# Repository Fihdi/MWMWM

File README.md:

# 6hp Wavefolder

MWMWM is a 7 to 1 Wavefolder based on [Daveys Deadband](https://github.com/DaveyGraham/Daveys_Deadband) and Buchlas wavefolding method. At the maximum amount of wavefolding, a single wave cycle gets converted into seven cycles on the output.

The **FOLD** and the **CV** knob settings control the amount of wavefolding. 

**OFFSET** is the second input and is summed to the **IN** signal. Like the **OFFSET** knob, it can be used to offset the **IN** signal.

Fully analog design allows for audio rate modulation. Every input and output jack is DC biased and thus the module can be used to modulate CV signals as well.

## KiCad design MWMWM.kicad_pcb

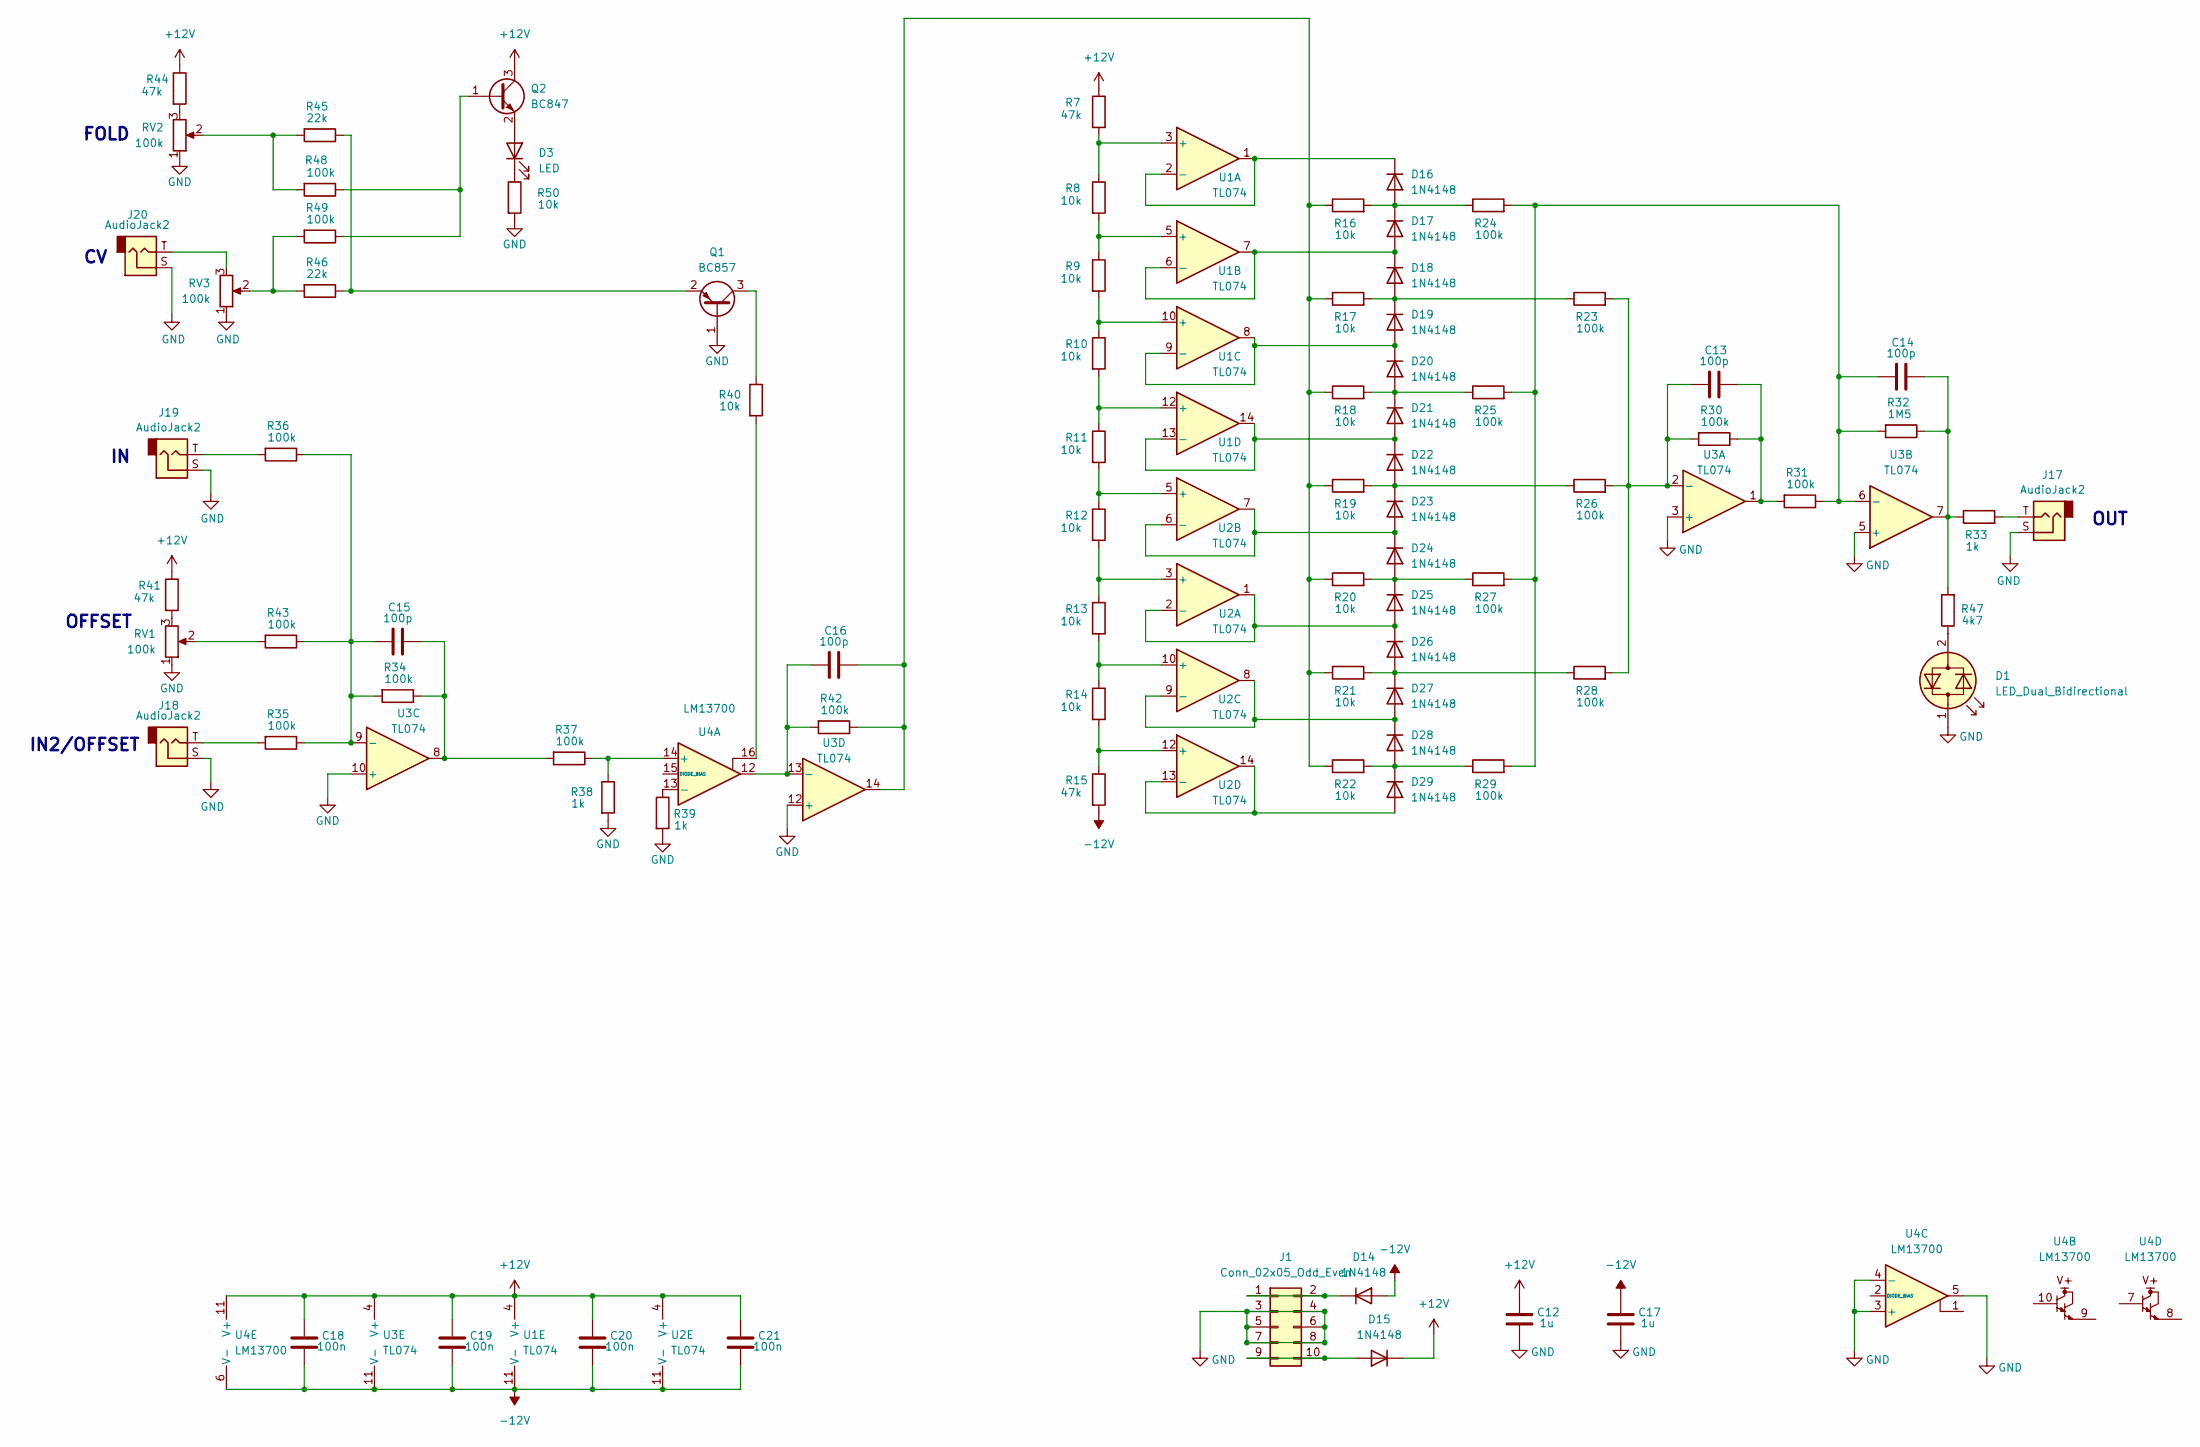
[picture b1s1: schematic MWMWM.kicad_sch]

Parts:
C12, C17: 1u; C_0805_2012Metric
C13, C14, C15, C16: 100p; C_0805_2012Metric
C18, C19, C20, C21: 100n; C_0805_2012Metric
D1: LED_Dual_Bidirectional; LED_D5.0mm
D3: LED; LED_D3.0mm
D14, D15, D16, D17, D18, D19, D20, D21, D22, D23, D24, D25, D26, D27, D28, D29: 1N4148; D_SOD-323_HandSoldering
J1: Conn_02x05_Odd_Even; IDC-Header_2x05_P2.54mm_Vertical
J17, J18, J19, J20: AudioJack2; MonoTRS
Q1: BC857; SOT-23
Q2: BC847; SOT-23
R7, R15, R41, R44: 47k; R_0805_2012Metric
R8, R9, R10, R11, R12, R13, R14, R16, R17, R18, R19, R20, R21, R22, R40, R50: 10k; R_0805_2012Metric
R23, R24, R25, R26, R27, R28, R29, R30, R31, R34, R35, R36, R37, R42, R43, R48, R49: 100k; R_0805_2012Metric
R32: 1M5; R_0805_2012Metric
R33, R38, R39: 1k; R_0805_2012Metric
R45, R46: 22k; R_0805_2012Metric
R47: 4k7; R_0805_2012Metric
RV1, RV2, RV3: 100k; Potentiometer_Alpha_RD901F-40-00D_Single_Vertical
U1, U2, U3: TL074; TSSOP-14_4.4x5mm_P0.65mm
U4: LM13700; SOIC-16_3.9x9.9mm_P1.27mm

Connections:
+12V: C12.1, C18.1, C19.1, C20.1, C21.1, D15.1 (K), Q2.3 (C), R7.1, R41.1, R44.1, U1.4 (V+), U2.4 (V+), U3.4 (V+), U4.11 (V+)
-12V: C17.1, C18.2, C19.2, C20.2, C21.2, D14.2 (A), R15.2, U1.11 (V-), U2.11 (V-), U3.11 (V-), U4.6 (V-)
GND: C12.2, C17.2, D1.1 (KA), J1.3, J1.4, J1.5, J1.6, J1.7, J1.8, J17.S, J18.S, J19.S, J20.S, Q1.1 (B), R38.2, R39.2, R50.2, RV1.1, RV2.1, RV3.1, U3.3 (+), U3.5 (+), U3.10 (+), U3.12 (+), U4.3 (+), U4.4 (-), U4.5
unnamed: C13.2, R30.1, R31.2, U3.1
unnamed: C14.2, R32.1, R33.1, R47.2, U3.7
unnamed: C15.2, R34.1, R37.2, U3.8
unnamed: C16.2, R16.1, R17.1, R18.1, R19.1, R20.1, R21.1, R22.1, R42.1, U3.14
unnamed: D1.2 (AK), R47.1
unnamed: D3.2 (A), Q2.2 (E)
unnamed: D3.1 (K), R50.1
unnamed: D14.1 (K), J1.1, J1.2
unnamed: D15.2 (A), J1.9, J1.10
unnamed: D16.2 (A), D17.1 (K), R16.2, R24.1
unnamed: D16.1 (K), U1.1, U1.2 (-)
unnamed: D17.2 (A), D18.1 (K), U1.6 (-), U1.7
unnamed: D18.2 (A), D19.1 (K), R17.2, R23.1
unnamed: D19.2 (A), D20.1 (K), U1.8, U1.9 (-)
unnamed: D20.2 (A), D21.1 (K), R18.2, R25.1
unnamed: D21.2 (A), D22.1 (K), U1.13 (-), U1.14
unnamed: D22.2 (A), D23.1 (K), R19.2, R26.1
unnamed: D23.2 (A), D24.1 (K), U2.6 (-), U2.7
unnamed: D24.2 (A), D25.1 (K), R20.2, R27.1
unnamed: D25.2 (A), D26.1 (K), U2.1, U2.2 (-)
unnamed: D26.2 (A), D27.1 (K), R21.2, R28.1
unnamed: D27.2 (A), D28.1 (K), U2.8, U2.9 (-)
unnamed: D28.2 (A), D29.1 (K), R22.2, R29.1
unnamed: D29.2 (A), U2.13 (-), U2.14
unnamed: J17.T, R33.2
unnamed: J18.T, R35.2
unnamed: J19.T, R36.2
unnamed: J20.T, RV3.3
unnamed: Q1.3 (C), R40.1
unnamed: Q1.2 (E), R45.1, R46.1
unnamed: Q2.1 (B), R48.1, R49.1
unnamed: R40.2, U4.16
unnamed: R41.2, RV1.3
unnamed: R43.2, RV1.2
unnamed: R44.2, RV2.3
unnamed: R45.2, R48.2, RV2.2
unnamed: R46.2, R49.2, RV3.2
unnamed: R7.2, R8.1, U1.3 (+)
unnamed: R8.2, R9.1, U1.5 (+)
unnamed: R9.2, R10.1, U1.10 (+)
unnamed: R10.2, R11.1, U1.12 (+)
unnamed: R12.2, R13.1, U2.3 (+)
unnamed: R11.2, R12.1, U2.5 (+)
unnamed: R13.2, R14.1, U2.10 (+)
unnamed: R14.2, R15.1, U2.12 (+)
unnamed: C13.1, R23.2, R26.2, R28.2, R30.2, U3.2 (-)
unnamed: C14.1, R24.2, R25.2, R27.2, R29.2, R31.1, R32.2, U3.6 (-)
unnamed: C15.1, R34.2, R35.1, R36.1, R43.1, U3.9 (-)
unnamed: C16.1, R42.2, U3.13 (-), U4.12
unnamed: R37.1, R38.1, U4.14 (+)
unnamed: R39.1, U4.13 (-)

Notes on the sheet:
OUT
IN2/OFFSET
OFFSET
FOLD

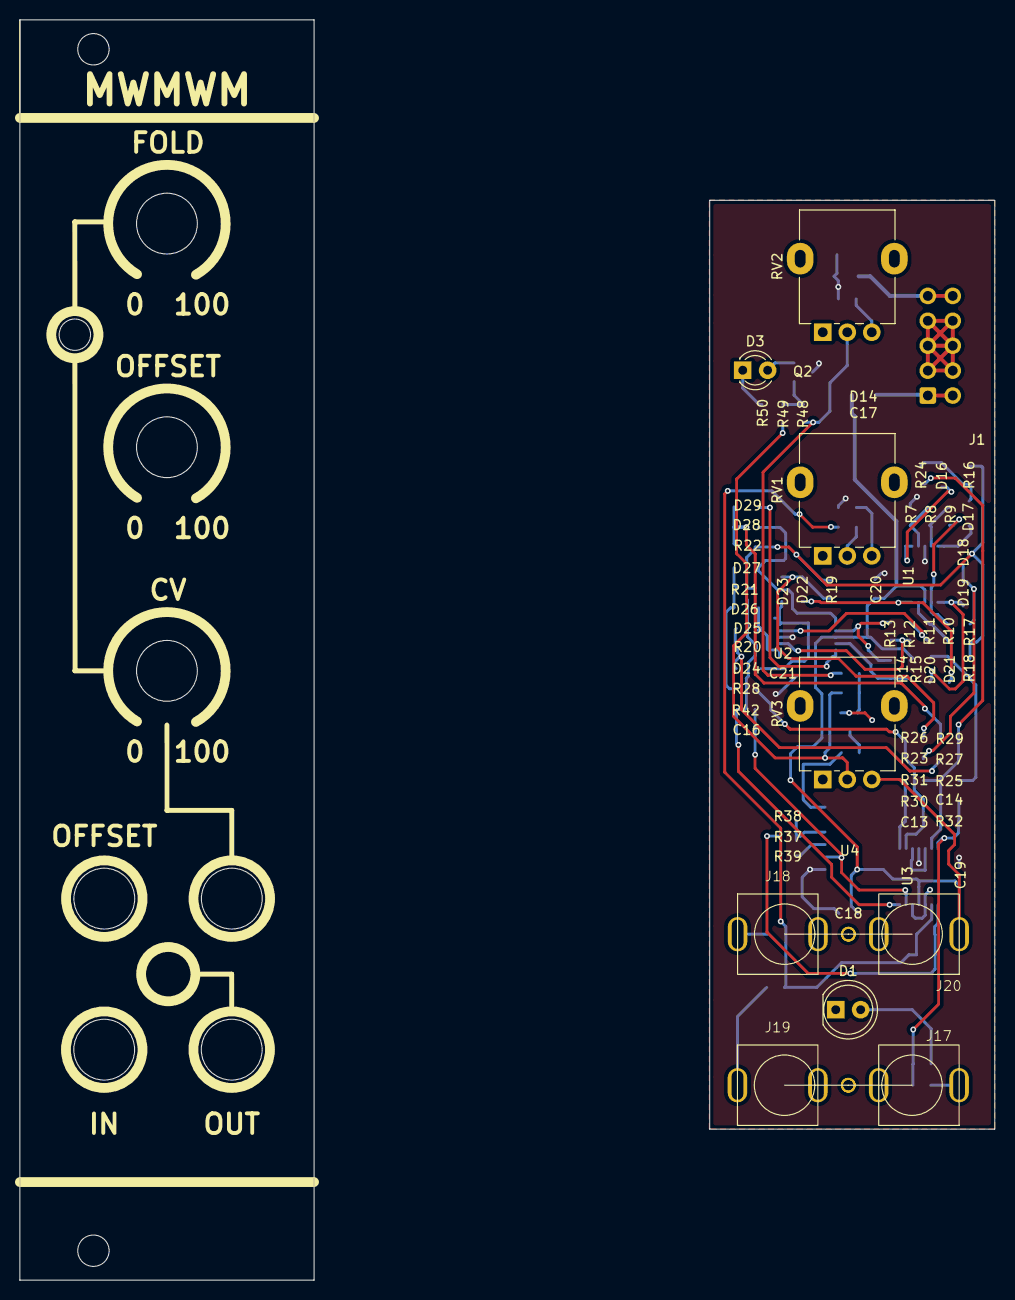
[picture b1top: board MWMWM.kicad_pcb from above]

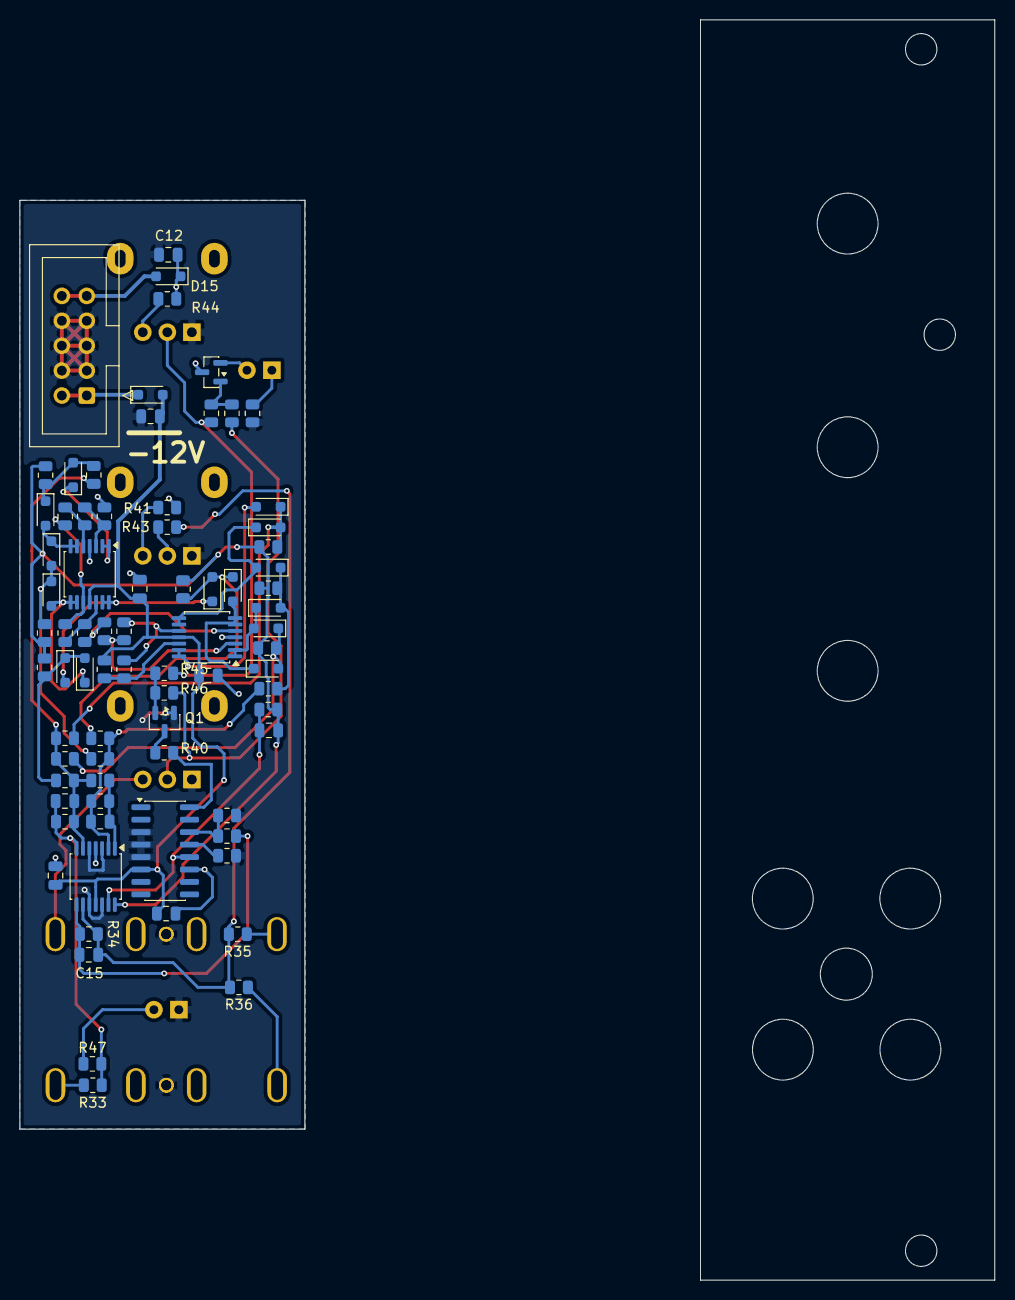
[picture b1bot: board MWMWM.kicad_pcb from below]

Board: 2 copper layers, 29.1 x 94.7 mm, 86 parts (77 on the bottom side), 54 nets.

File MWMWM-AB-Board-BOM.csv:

"Reference","Qty","Value","Footprint"
"C12,C17","2","1u","Capacitor_SMD:C_0805_2012Metric"
"C13,C14,C15,C16","4","100p","Capacitor_SMD:C_0805_2012Metric"
"C18,C19,C20,C21","4","100n","Capacitor_SMD:C_0805_2012Metric"
"D1","1","LED_Dual_Bidirectional","LED_THT:LED_D5.0mm"
"D3","1","LED","LED_THT:LED_D3.0mm"
"D14,D15,D16,D17,D18,D19,D20,D21,D22,D23,D24,D25,D26,D27,D28,D29","16","1N4148","Diode_SMD:D_SOD-323_HandSoldering"
"J1","1","Conn_02x05_Odd_Even","Connector_IDC:IDC-Header_2x05_P2.54mm_Vertical"
"J17,J18,J19,J20","4","AudioJack2","Library:MonoTRS"
"Q1","1","BC857","Package_TO_SOT_SMD:SOT-23"
"Q2","1","BC847","Package_TO_SOT_SMD:SOT-23"
"R7,R15,R41,R44","4","47k","Resistor_SMD:R_0805_2012Metric"
"R8,R9,R10,R11,R12,R13,R14,R16,R17,R18,R19,R20,R21,R22,R40,R50","16","10k","Resistor_SMD:R_0805_2012Metric"
"R23,R24,R25,R26,R27,R28,R29,R30,R31,R34,R35,R36,R37,R42,R43,R48,R49","17","100k","Resistor_SMD:R_0805_2012Metric"
"R32","1","1M5","Resistor_SMD:R_0805_2012Metric"
"R33,R38,R39","3","1k","Resistor_SMD:R_0805_2012Metric"
"R45,R46","2","22k","Resistor_SMD:R_0805_2012Metric"
"R47","1","4k7","Resistor_SMD:R_0805_2012Metric"
"RV1,RV2,RV3","3","100k","Potentiometer_THT:Potentiometer_Alpha_RD901F-40-00D_Single_Vertical"
"U1,U2,U3","3","TL074","Package_SO:TSSOP-14_4.4x5mm_P0.65mm"
"U4","1","LM13700","Package_SO:SOIC-16_3.9x9.9mm_P1.27mm"
